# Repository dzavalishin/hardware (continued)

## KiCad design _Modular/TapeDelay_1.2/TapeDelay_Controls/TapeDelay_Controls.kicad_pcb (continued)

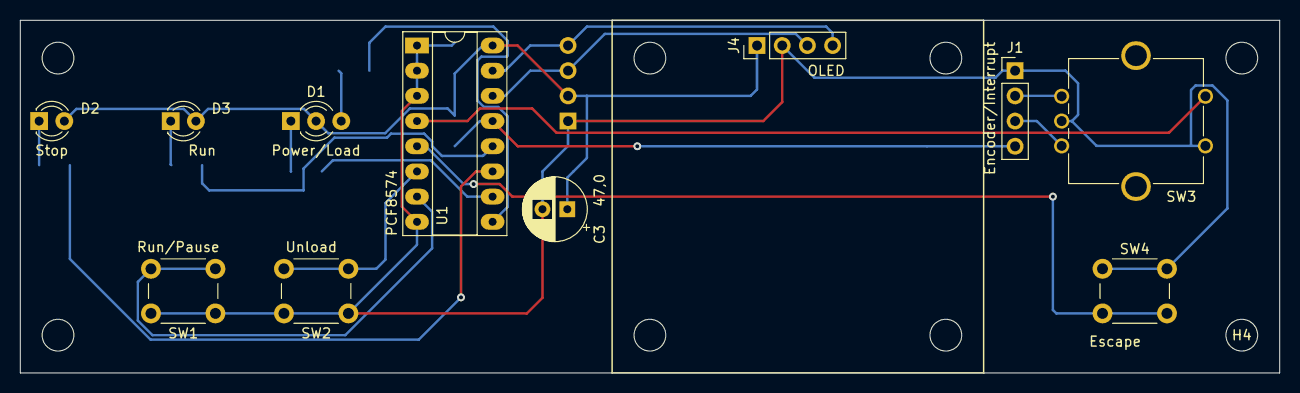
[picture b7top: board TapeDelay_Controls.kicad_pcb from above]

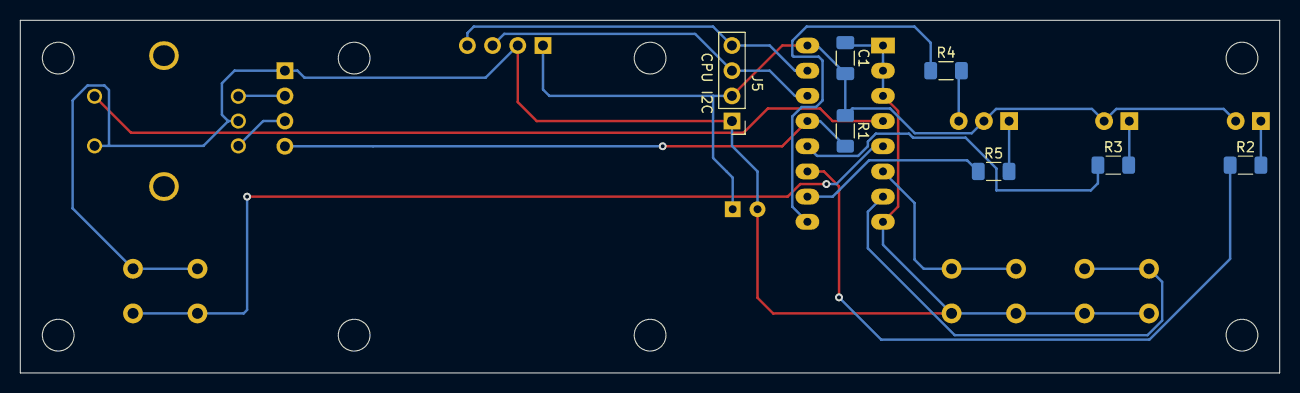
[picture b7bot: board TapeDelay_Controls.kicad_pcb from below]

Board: 2 copper layers, 127.0 x 35.6 mm, 26 parts (7 on the bottom side), 19 nets.

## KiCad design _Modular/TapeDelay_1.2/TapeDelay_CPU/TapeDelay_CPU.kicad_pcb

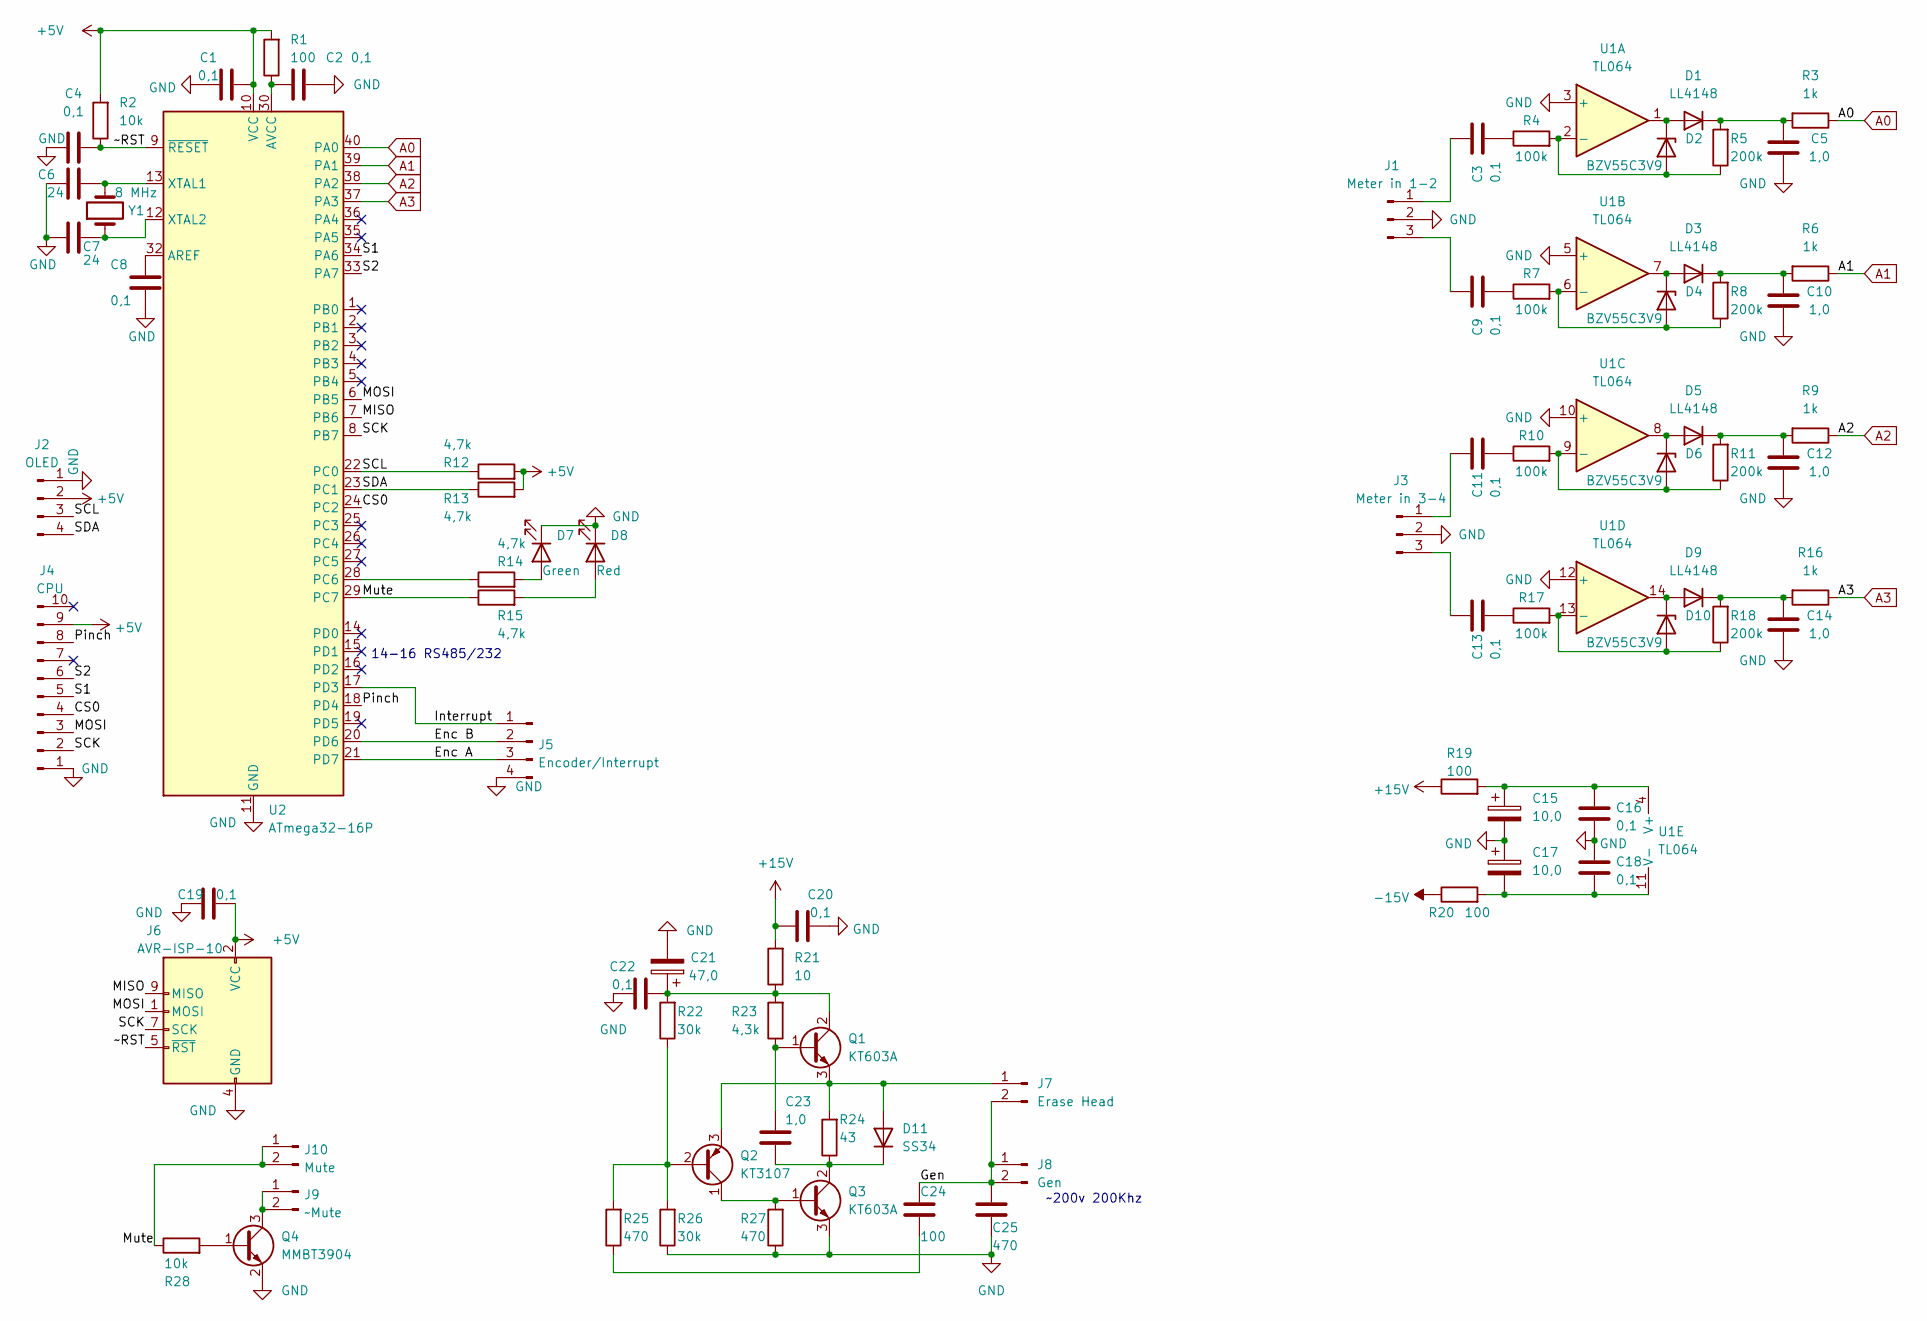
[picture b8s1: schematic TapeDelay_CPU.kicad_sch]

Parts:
C1, C2, C3, C4, C8, C9, C11, C13, C16, C18, C19: 0,1; C_1206_3216Metric_Pad1.33x1.80mm_HandSolder
C5, C10, C12, C14, C23: 1,0; C_0805_2012Metric_Pad1.18x1.45mm_HandSolder
C6, C7: 24; C_0805_2012Metric_Pad1.18x1.45mm_HandSolder
C15, C17: 10,0; C_0805_2012Metric_Pad1.18x1.45mm_HandSolder
C20, C22: 0,1; C_0805_2012Metric_Pad1.18x1.45mm_HandSolder
C21: 47,0; CP_Radial_D6.3mm_P2.50mm
C24: 100; C_Disc_D5.0mm_W2.5mm_P2.50mm
C25: 470; C_Disc_D5.0mm_W2.5mm_P2.50mm
D1, D3, D5, D9: LL4148; D_MiniMELF
D2, D4, D6, D10: BZV55C3V9; D_MiniMELF
D7: Green; LED_1206_3216Metric_Pad1.42x1.75mm_HandSolder
D8: Red; LED_1206_3216Metric_Pad1.42x1.75mm_HandSolder
D11: SS34; D_SMA-SMB_Universal_Handsoldering
J1: Meter in 1-2; PinHeader_1x03_P2.54mm_Vertical
J2: OLED; PinHeader_1x04_P2.54mm_Horizontal
J3: Meter in 3-4; PinHeader_1x03_P2.54mm_Vertical
J4: CPU; PinHeader_1x10_P2.54mm_Horizontal
J5: Encoder/Interrupt; PinHeader_1x04_P2.54mm_Horizontal
J6: AVR-ISP-10; PinHeader_2x05_P2.54mm_Vertical
J7: Erase Head; PinHeader_1x02_P2.54mm_Vertical
J8: Gen; PinHeader_1x02_P2.54mm_Vertical
J9: ~Mute; PinHeader_1x02_P2.54mm_Vertical
J10: Mute; PinHeader_1x02_P2.54mm_Vertical
Q1, Q3: KT603A; TO-92_Wide
Q2: KT3107; TO-92
Q4: MMBT3904; SOT-23
R1, R19, R20: 100; R_1206_3216Metric_Pad1.30x1.75mm_HandSolder
R2, R28: 10k; R_1206_3216Metric_Pad1.30x1.75mm_HandSolder
R3, R6, R9, R16: 1k; R_1206_3216Metric_Pad1.30x1.75mm_HandSolder
R4, R7, R10, R17: 100k; R_1206_3216Metric_Pad1.30x1.75mm_HandSolder
R5, R8, R11, R18: 200k; R_1206_3216Metric_Pad1.30x1.75mm_HandSolder
R12, R13, R14, R15: 4,7k; R_1206_3216Metric_Pad1.30x1.75mm_HandSolder
R21: 10; R_Axial_DIN0309_L9.0mm_D3.2mm_P2.54mm_Vertical
R22, R26: 30k; R_1206_3216Metric_Pad1.30x1.75mm_HandSolder
R23: 4,3k; R_1206_3216Metric_Pad1.30x1.75mm_HandSolder
R24: 43; R_Axial_DIN0309_L9.0mm_D3.2mm_P2.54mm_Vertical
R25, R27: 470; R_1206_3216Metric_Pad1.30x1.75mm_HandSolder
U1: TL064; DIP-14_W7.62mm_Socket_LongPads
U2: ATmega32-16P; DIP-40_W15.24mm_Socket_LongPads
Y1: 8 MHz; Crystal_HC49-U_Vertical

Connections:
+5V: C1.2, C19.2, J2.2, J4.9, J6.2 (VCC), R1.2, R2.2, R12.2, R13.2, U2.10 (VCC)
+15V: C20.2, R19.1, R21.2
-15V: R20.1
/CS0: J4.4, U2.24 (PC2)
/Enc A: J5.3, U2.21 (PD7)
/Enc B: J5.2, U2.20 (PD6)
/Gen: C24.2, C25.2, J7.2, J8.1, J8.2
/Interrupt: J5.1, U2.17 (PD3)
/MISO: J6.9 (MISO), U2.7 (PB6)
/MOSI: J4.3, J6.1 (MOSI), U2.6 (PB5)
/Mute: J10.1, J10.2, R15.1, R28.1, U2.29 (PC7)
/Pinch: J4.8, U2.18 (PD4)
/S1: J4.5, U2.34 (PA6)
/S2: J4.6, U2.33 (PA7)
/SCK: J4.2, J6.7 (SCK), U2.8 (PB7)
/SCL: J2.3, R12.1, U2.22 (PC0)
/SDA: J2.4, R13.1, U2.23 (PC1)
/~RST: C4.2, J6.5 (~RST), R2.1, U2.9 (~RESET)
A0: R3.1, U2.40 (PA0)
A1: R6.1, U2.39 (PA1)
A2: R9.1, U2.38 (PA2)
A3: R16.1, U2.37 (PA3)
GND: C1.1, C2.2, C4.1, C5.1, C6.2, C7.2, C8.2, C10.1, C12.1, C14.1, C15.2, C16.2, C17.1, C18.1, C19.1, C20.1, C21.2, C22.2, C25.1, D7.1 (K), D8.1 (K), J1.2, J2.1, J3.2, J4.1, J5.4, J6.4 (GND), J6.6 (GND), J6.8 (GND), J6.10 (GND), Q3.3 (E), Q4.2 (E), R26.1, R27.1, U1.3 (+), U1.5 (+), U1.10 (+), U1.12 (+), U2.11 (GND), U2.31 (GND)
unnamed: C2.1, R1.1, U2.30 (AVCC)
unnamed: C3.1, J1.1
unnamed: C3.2, R4.1
unnamed: C5.2, D1.1 (K), R3.2, R5.2
unnamed: C6.1, U2.13 (XTAL1), Y1.2
unnamed: C7.1, U2.12 (XTAL2), Y1.1
unnamed: C8.1, U2.32 (AREF)
unnamed: C9.1, J1.3
unnamed: C9.2, R7.1
unnamed: C10.2, D3.1 (K), R6.2, R8.2
unnamed: C11.1, J3.1
unnamed: C11.2, R10.1
unnamed: C12.2, D5.1 (K), R9.2, R11.2
unnamed: C13.1, J3.3
unnamed: C13.2, R17.1
unnamed: C14.2, D9.1 (K), R16.2, R18.2
unnamed: C15.1, C16.1, R19.2, U1.4 (V+)
unnamed: C17.2, C18.2, R20.2, U1.11 (V-)
unnamed: C21.1, C22.1, Q1.2 (C), R21.1, R22.2, R23.2
unnamed: C23.1, D11.1 (K), Q3.2 (C), R24.1
unnamed: C23.2, Q1.1 (B), R23.1
unnamed: C24.1, R25.1
unnamed: D1.2 (A), D2.1 (K), U1.1
unnamed: D2.2 (A), R4.2, R5.1, U1.2 (-)
unnamed: D3.2 (A), D4.1 (K), U1.7
unnamed: D4.2 (A), R7.2, R8.1, U1.6 (-)
unnamed: D5.2 (A), D6.1 (K), U1.8
unnamed: D6.2 (A), R10.2, R11.1, U1.9 (-)
unnamed: D7.2 (A), R14.2
unnamed: D8.2 (A), R15.2
unnamed: D9.2 (A), D10.1 (K), U1.14
unnamed: D10.2 (A), R17.2, R18.1, U1.13 (-)
unnamed: D11.2 (A), J7.1, Q1.3 (E), Q2.3 (E), R24.2
unnamed: J9.1, J9.2, Q4.3 (C)
unnamed: Q2.1 (C), Q3.1 (B), R27.2
unnamed: Q2.2 (B), R22.1, R25.2, R26.2
unnamed: Q4.1 (B), R28.2
unnamed: R14.1, U2.28 (PC6)

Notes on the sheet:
14-16 RS485/232
~200v 200Khz

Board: 2 copper layers, 81 parts (43 on the bottom side), 60 nets, no tracks yet.

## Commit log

2017-10-25 import
2018-01-11 Capacitive sensor
2018-01-11 ta7281
2018-04-14 template
2018-11-13 Restructure
2023-06-02 headph amp, level meter
2023-06-06 add tape delay
2023-06-07 footpr
2023-06-08 separate power pcb
2023-06-10 Sensors
2023-06-12 Plot
2023-06-12 sens
2023-06-12 tighter
2023-06-12 pinch
2023-06-12 solenoid
2023-06-13 tape box
2023-06-13 cleaner
2023-06-15 tape box details
2023-06-15 faceplate
2023-06-21 meter
2023-06-21 meter pcb
2023-06-21 tape
2023-08-31 Solenoid control by motors
2023-10-11 320x240 color meters
